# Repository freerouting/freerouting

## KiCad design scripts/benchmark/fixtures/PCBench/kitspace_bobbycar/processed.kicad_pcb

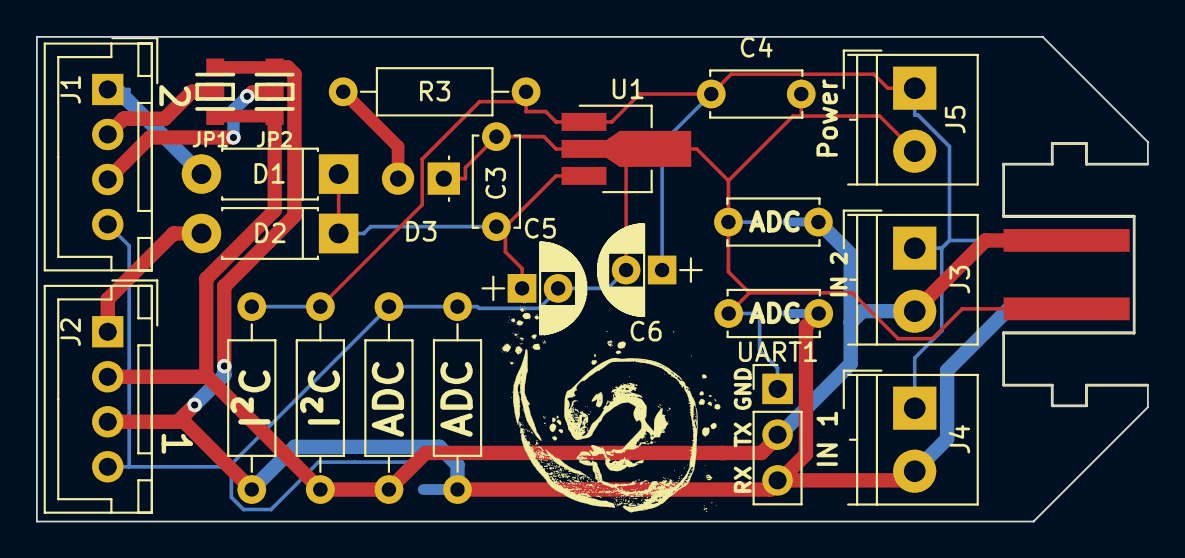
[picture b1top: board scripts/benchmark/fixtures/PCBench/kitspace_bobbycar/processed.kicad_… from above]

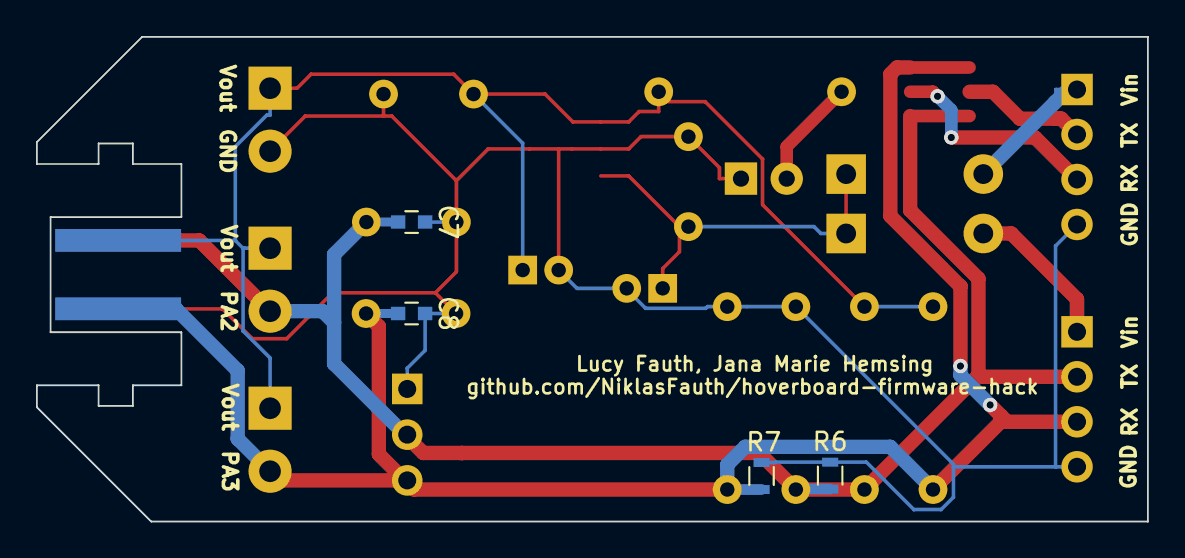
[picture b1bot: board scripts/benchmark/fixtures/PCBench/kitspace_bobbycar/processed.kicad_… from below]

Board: 2 copper layers, 61.7 x 26.9 mm, 28 parts (4 on the bottom side), 10 nets.

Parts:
C1, C2: C_Small; C_Disc_D5.0mm_W2.5mm_P5.00mm
C3, C4: 1uF; C_Disc_D5.0mm_W2.5mm_P5.00mm
C5, C6: 22uF; CP_Radial_D5.0mm_P2.00mm
C7, C8: C_Small; C_0603
D1, D2: D; D_DO-41_SOD81_P7.62mm_Horizontal
D3: LED; LED_D3.0mm
J1, J2: Conn_01x04; JST_XH_B04B-XH-A_04x2.50mm_Straight
J3, J4, J5: Screw_Terminal_01x02; TerminalBlock_4UCON_19963_02x3.5mm_Straight
J6: Conn_01x04; NUNCHUCK
JP1, JP2: Jumper_NC_Dual; SOLDER-JUMPER_2-WAY
R1, R2: R_Small; R_Axial_DIN0207_L6.3mm_D2.5mm_P10.16mm_Horizontal
R3: 220Ohm; R_Axial_DIN0207_L6.3mm_D2.5mm_P10.16mm_Horizontal
R4, R5: 3k3; R_Axial_DIN0207_L6.3mm_D2.5mm_P10.16mm_Horizontal
R6, R7: R_Small; R_0603
U1: L7805SOT89; SOT-89-3_Handsoldering
UART1: Conn_01x03; Pin_Header_Straight_1x03_Pitch2.54mm

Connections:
GND: C1.1, C2.2, C3.2, C4.2, C5.2, C6.2, C7.1, C8.2, D3.1, J1.4, J2.4, J5.2, J6.1, R1.1, R2.2, R6.1, R7.2, U1.2, UART1.1
unnamed: D1.2, J1.1
unnamed: D2.2, J2.1
unnamed: D3.2, R3.1
RX: C2.1, C8.1, J2.3, J4.2, J6.4, JP1.3, JP2.3, R2.1, R4.2, R7.1, UART1.3
RX.1: J1.3, JP2.2
TX: C1.2, C7.2, J2.2, J3.2, J6.2, JP1.1, JP2.1, R1.2, R5.2, R6.2, UART1.2
TX.1: J1.2, JP1.2
VCC: C4.1, C6.1, J3.1, J4.1, J5.1, J6.3, R3.2, R4.1, R5.1, U1.1
VDD: C3.1, C5.1, D1.1, D2.1, U1.3

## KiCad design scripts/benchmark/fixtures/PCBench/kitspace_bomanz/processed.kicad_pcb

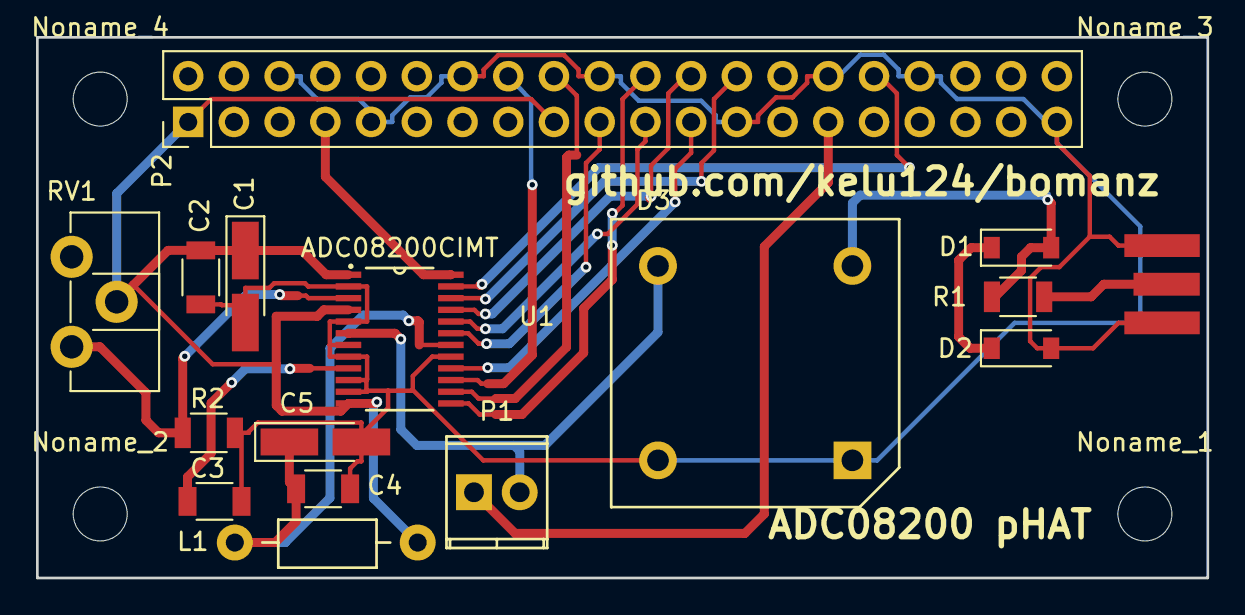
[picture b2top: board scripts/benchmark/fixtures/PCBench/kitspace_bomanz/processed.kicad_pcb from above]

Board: 2 copper layers, 65.0 x 30.0 mm, 20 parts (0 on the bottom side), 20 nets.

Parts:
C1, C5: CP_Tantalum_Case-A_EIA-3216-18_Hand
C2, C3, C4: C_1206
D1, D2: D_SOD-123
D3: Diode_Bridge_15.7x15.7
L1: Choke_Horizontal_RM10mm
Noname_1, Noname_2, Noname_3, Noname_4: MountingHole_3mm
Noname_5: SMA_EDGE
P1: TerminalBlock_Pheonix_MPT-2.54mm_2pol
P2: Pin_Header_Straight_2x20_Pitch2.54mm
R1, R2: R_1206
RV1: Potentiometer_Trimmer_ACP_CA9h2.5_Vertical_Px2.5mm_Py5.0mm
U1: ADC08200CIMT; ADC08200_PW_24

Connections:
+3V3: C1.1, C2.1, L1.1, P2.1, P2.17, RV1.2, U1.1, U1.4, U1.12
CLK: P2.7, U1.24
D0: P2.26, U1.22
D1: P2.24, U1.21
D2: P2.21, U1.20
D3: P2.19, U1.19
D4: P2.23, U1.16
D5: P2.16, U1.15
D6: P2.18, U1.14
D7: P2.22, U1.13
DM: P2.32, U1.23
GND: C1.2, C2.2, C3.2, C4.2, C5.2, D2.2, D3.2, D3.3, Noname_5.2, P2.6, P2.9, P2.14, P2.20, P2.25, P2.30, P2.34, P2.39, R2.2, U1.2, U1.5, U1.7, U1.8, U1.10, U1.11, U1.17
IN: P1.1, P2.29
unnamed: C3.1, U1.9
unnamed: C4.1, C5.1, L1.2, U1.18
unnamed: D1.1, D2.1
unnamed: D1.2, D3.4, R1.1
unnamed: D3.1, P1.2, U1.6
unnamed: Noname_5.1, R1.2
unnamed: R2.1, RV1.3, U1.3

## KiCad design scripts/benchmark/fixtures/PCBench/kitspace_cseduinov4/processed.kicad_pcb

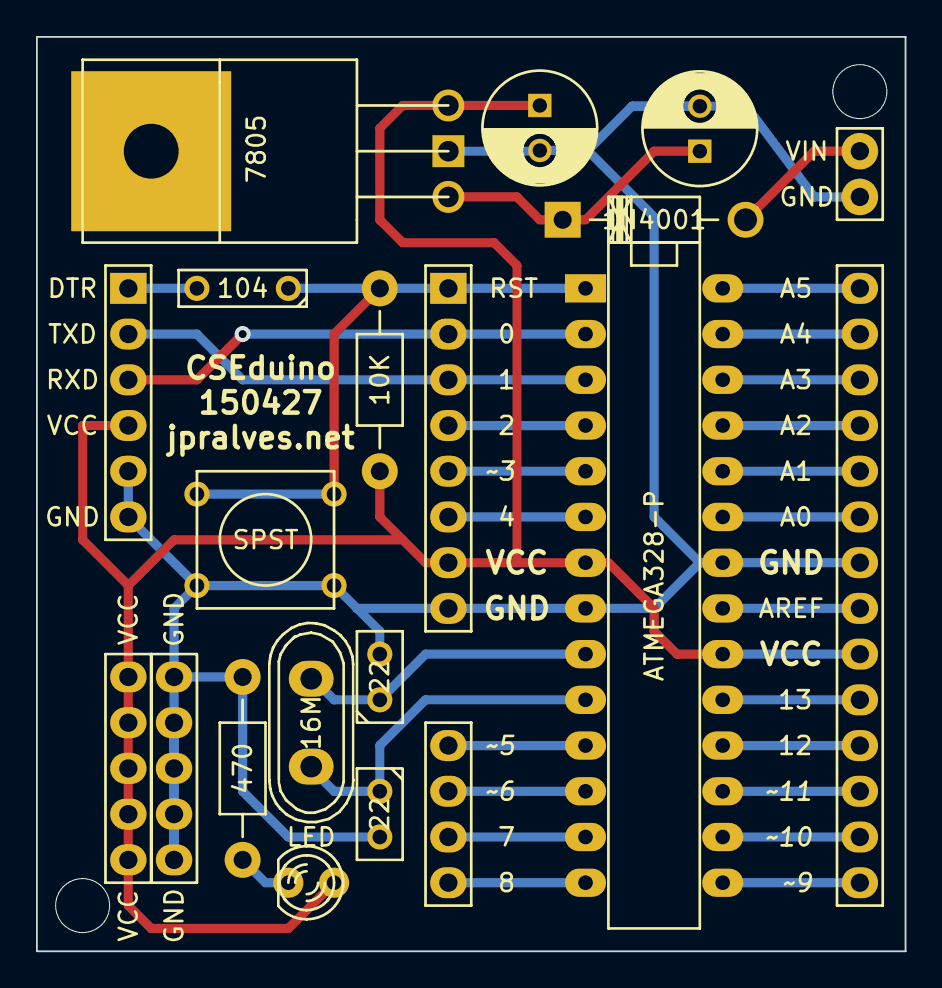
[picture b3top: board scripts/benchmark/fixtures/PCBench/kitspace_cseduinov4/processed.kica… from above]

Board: 2 copper layers, 48.3 x 50.8 mm, 18 parts (0 on the bottom side), 30 nets.

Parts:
C1, C2: 100uF; C_Radial_D6.3_L11.2_P2.5
C3, C4: 22; C1
C5: 104; C2
D1: 1N4001; Diode_DO-41_SOD81_Horizontal_RM10
D2: LED; LED-3MM
IC1: ATMEGA328-P; DIP-28__300_ELL
P1: CONN_01X02; Pin_Header_Straight_1x02
P2: CONN_01X14; Pin_Header_Straight_1x14
P3: CONN_01X04; Pin_Header_Straight_1x04
P4: CONN_01X08; Pin_Header_Straight_1x08
P5: CONN_01X06; Pin_Header_Straight_1x06
R1: 470; Resistor_Horizontal_RM10mm
R2: 10K; Resistor_Horizontal_RM10mm
SW1: SPST; SW_PUSH_SMALL
U1: 7805; LM78XX
X1: 16M; Crystal_HC50-U_Vertical

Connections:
+5V: C2.1, D2.1, IC1.7, IC1.20, P2.6, P4.7, P5.4, R2.1, U1.VO
GND: C1.2, C2.2, C3.2, C4.2, IC1.8, IC1.22, P1.2, P2.8, P4.8, P5.5, P5.6, R1.2, SW1.2, U1.GND
unnamed: C1.1, D1.2, U1.VI
unnamed: C3.1, IC1.10, X1.1
unnamed: C4.1, IC1.9, X1.2
unnamed: C5.1, IC1.1, P4.1, R2.2, SW1.1
unnamed: C5.2, P5.1
unnamed: D1.1, P1.1
unnamed: D2.2, R1.1
unnamed: IC1.2, P4.2, P5.3
unnamed: IC1.3, P4.3, P5.2
unnamed: IC1.4, P4.4
unnamed: IC1.5, P4.5
unnamed: IC1.6, P4.6
unnamed: IC1.11, P3.1
unnamed: IC1.12, P3.2
unnamed: IC1.13, P3.3
unnamed: IC1.14, P3.4
unnamed: IC1.15, P2.1
unnamed: IC1.16, P2.2
unnamed: IC1.17, P2.3
unnamed: IC1.18, P2.4
unnamed: IC1.19, P2.5
unnamed: IC1.21, P2.7
unnamed: IC1.23, P2.9
unnamed: IC1.24, P2.10
unnamed: IC1.25, P2.11
unnamed: IC1.26, P2.12
unnamed: IC1.27, P2.13
unnamed: IC1.28, P2.14

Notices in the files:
parts and their libraries:
Copyright 2016 Accelerated Designs. All rights reserved.
